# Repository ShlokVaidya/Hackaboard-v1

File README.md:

# 🎹 Hackaboard - The Hackaboard Keyboard

Welcome to **Hackaboard**, a beautifully crafted **63% mechanical keyboard** that combines aesthetics, functionality, and a touch of personality. A versatile keyboard designed to elevate your typing experience.

---

## ✨ What is Hackaboard?

Hackaboard is a custom mechanical keyboard featuring a 63% layout with modern conveniences like an **OLED display**, **rotary encoder**, and **full programmability**. Whether you're a developer, writer, designer, or gamer, this keyboard adapts to your workflow with support for multiple keymap configurations.

---

## 📸 Gallery

Take a look at the Hackaboard in all its glory:

---

## 🎯 Key Features

### Hardware Specs
- **Layout:** 63% compact form factor (63 keys)
- **Microcontroller:** Raspberry Pi Pico 2W (RP2350, supports QMK firmware)
- **Matrix:** 5 rows × 15 columns (COL2ROW configuration)
- **Switch Type:** Cherry MX PCB hotswap compatible
- **Display:** SSD1306 0.91" OLED (128x32 pixels)
- **Input:** EC11 Rotary Encoder with knob support
- **Debounce:** 5ms for reliable key registration

### Software Capabilities
- **Firmware:** QMK-compatible with custom configuration
- **Encoder:** Customizable rotary encoder with 4-level resolution
- **MIDI Support:** Full MIDI protocol implementation for music applications
- **Macros:** Built-in email address macro with right shift + 2
- **Keymaps:** Multiple pre-configured layouts (see below)

Please read [the Journal](./hackaboard-journal.md)
---

## ⌨️ Keymap Configurations

Hackaboard comes with **4 pre-built keymaps** to suit different typing styles and use cases:

### 1. **Default Keymap**
The standard ANSI layout – perfect for everyday typing and programming.

### 2. **Photographer Keymap**
Optimized for photo editing workflows with custom shortcuts and macro assignments.

### 3. **Writer Keymap**
Specialized layout for content creators with quick-access keys for common writing functions.

### 4. **VIA-Compatible Keymap**
Full support for the VIA configurator, allowing you to reprogram your keyboard without touching code.

---

# BOM table

Category | Item | Website | Cost (INR) | Cost (USD)
-- | -- | -- | -- | --
MCU | Raspberry Pi Pico 2 | Robu.in | ₹544 | $6
Diodes | 1N4148 SOD-123 (×63) | Robu.in | ₹36 | $0.4
Shipping (MCU + diodes) | — | Robu.in | ₹49 | $0.54
Subtotal (MCU + diodes) |   |   | ₹630 | $7
Conversion fee (3%) |   |   | ₹650 | $7.22
MCU + Diodes Total |   |   | ₹650 | $7.22
PCB | 2-layer PCB (base settings, incl. GST + shipping) | LionCircuits | ₹5,281 | $58.68
Conversion fee (3%) |   |   | ₹159 | $1.77
PCB Total |   |   | ₹5,440 | $60.45
Switches + Stabilizers + Hotswap sockets | (x45 + x10 pack) | StacksKB | ₹3,604 | $40.04
Conversion fee (3%) |   |   | ₹108 | $1.20
Switches Total |   |   | ₹3,712 | $41.24
Keycaps | Full keycap set | CuriosityCaps | ₹1,999 | $22.21
Conversion fee (3%) |   |   | ₹59 | $0.66
Keycaps Total |   |   | ₹2,058 | $22.87
Non-metal Plate | Plate | robu.in | Rs 330 | 3.6 USD
Screws | | onlyscrews.in | Rs 400 | 4.5 USD
0.91" OLED | | I have
Potentiometer | | I have

And i need 3d printing from #printing-legion so that's Rs 820 or **9 USD**.

## Total
Currency | Total
-- | --
INR | ₹13,400
USD | $147.25 

---

## 🛠️ File Structure

```
Hackaboard-v1/
├── keyboards/hackaboard/         # Main keyboard configuration
│   ├── config.h                  # Hardware configuration
│   ├── info.json                 # Layout and metadata
│   ├── hackaboard.c              # Firmware logic
│   ├── hackaboard.h              # Firmware headers
│   ├── rules.mk                  # Build rules
│   └── keymaps/                  # Keymap definitions
│       ├── default/              # Default layout
│       ├── photographer/         # Photo editing optimized
│       ├── writer/               # Content creation optimized
│       └── via/                  # VIA configurator support
├── PCB/                          # KiCAD PCB design files
│   ├── hackaboard.kicad_sch      # Schematic
│   ├── hackaboard.kicad_pcb      # PCB layout
│   └── production/               # Manufacturing files (BOM, positions)
├── CAD/                          # 3D models and mechanical design
│   ├── case/                     # Keyboard case designs
│   └── plate/                    # Stabilizer plate designs
└── images/                       # Product photography
```

---

## 🚀 Getting Started

### Prerequisites
- QMK Firmware environment set up ([QMK Docs](https://docs.qmk.fm/))
- Python 3.6+ and pip
- ARM GCC toolchain (for RP2350)

### Building the Firmware

1. **Clone the QMK repository** and copy the Hackaboard firmware:
   ```bash
   git clone https://github.com/qmk/qmk_firmware.git
   cp -r keyboards/hackaboard/ qmk_firmware/keyboards/
   ```

2. **Build your preferred keymap:**
   ```bash
   qmk compile -kb hackaboard -km default
   ```

3. **Flash to your keyboard:**
   ```bash
   qmk flash -kb hackaboard -km default
   ```

### VIA Support
If you prefer a graphical interface, use the **VIA configurator**:
1. Download [VIA](https://www.caniusevia.com/)
2. Load the VIA keymap onto your Hackaboard
3. Customize in real-time without reflashing

---

## 🎨 Customization

### Rotary Encoder
The EC11 encoder on Hackaboard can be customized for:
- Volume control
- Scroll wheel simulation
- Layer switching
- Application shortcuts

### OLED Display
The tiny 0.91" OLED shows:
- Current layer information
- Keyboard status
- Custom animations
- Typing statistics

### Email Macro
Quickly insert your email address:
- **Key Combo:** Right Shift + 2
- **Default:** `shlokvaidya.in@gmail.com.com` (customize in `config.h`)

---

## 🔧 Advanced Features

### MIDI Mode
Hackaboard supports MIDI communication for:
- Virtual instrument control
- DAW integration
- Music production workflows

### Debounce Tuning
Adjust key sensitivity without reflashing:
- Current debounce: 5ms
- Modify `DEBOUNCE` in `config.h` if needed

### Custom Firmware Logic
Edit `hackaboard.c` and `hackaboard.h` to add:
- Complex macros
- Display animations
- Sensor integrations
- Hardware customizations

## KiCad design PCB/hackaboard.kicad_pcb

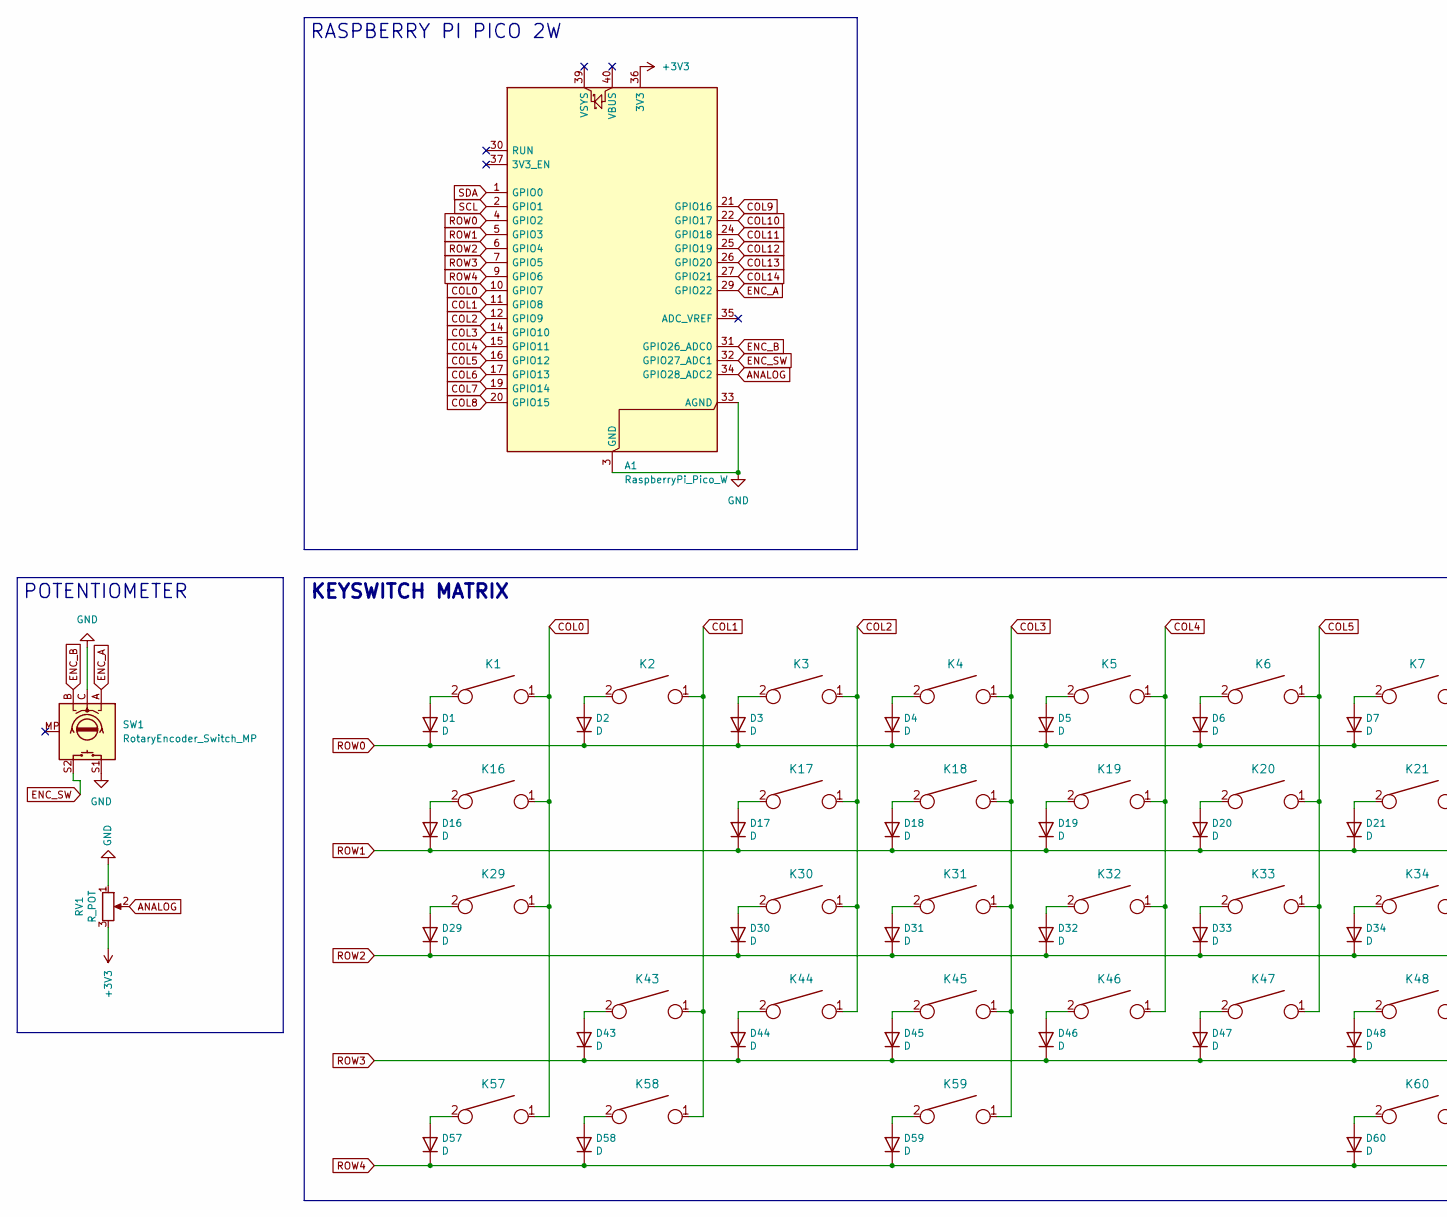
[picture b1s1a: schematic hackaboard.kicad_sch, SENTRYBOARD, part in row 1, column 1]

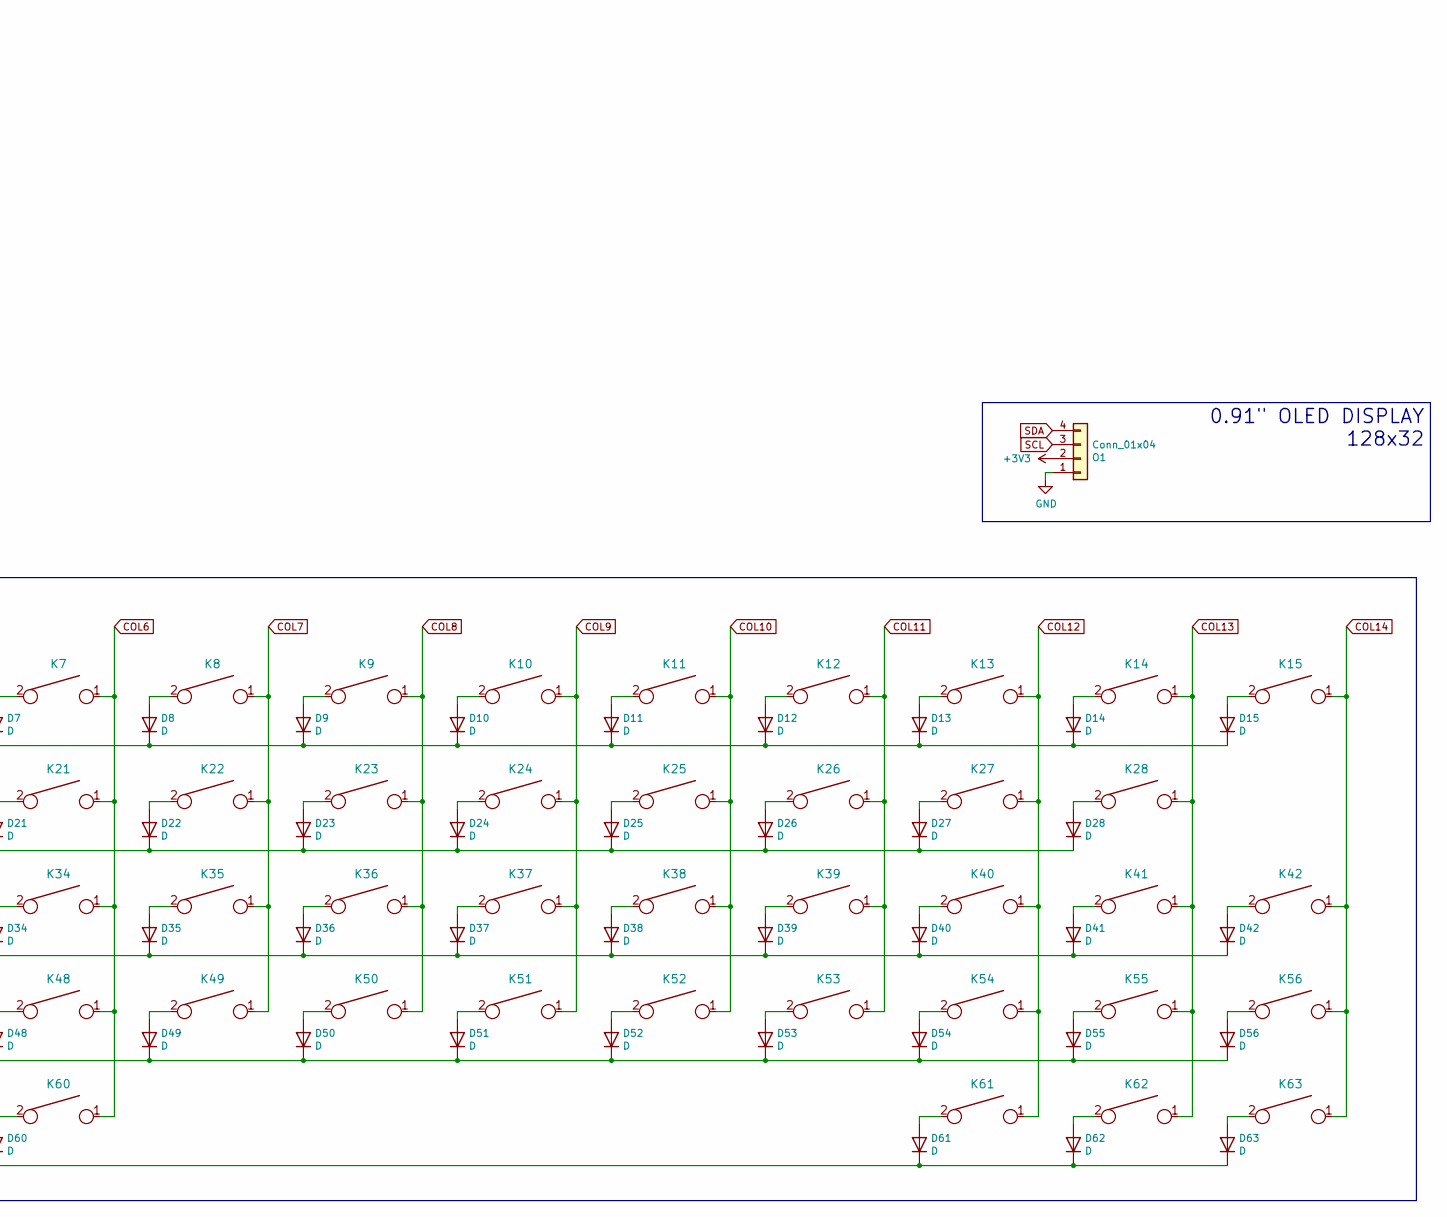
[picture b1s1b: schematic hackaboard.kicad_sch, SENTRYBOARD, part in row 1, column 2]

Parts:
A1: RaspberryPi_Pico_W; RaspberryPi_Pico_SMD_HandSolder
D1, D2, D3, D4, D5, D6, D7, D8, D9, D10, D11, D12, D13, D14, D15, D16, D17, D18, D19, D20, D21, D22, D23, D24, D25, D26, D27, D28, D29, D30, D31, D32, D33, D34, D35, D36, D37, D38, D39, D40, D41, D42, D43, D44, D45, D46, D47, D48, D49, D50, D51, D52, D53, D54, D55, D56, D57, D58, D59, D60, D61, D62, D63: D; D_SOD-123
K1, K2, K3, K4, K5, K6, K7, K8, K9, K10, K11, K12, K13, K14, K15, K17, K18, K19, K20, K21, K22, K23, K24, K25, K26, K27, K28, K30, K31, K32, K33, K34, K35, K36, K37, K38, K39, K40, K41, K44, K45, K46, K47, K48, K49, K50, K51, K52, K53, K54, K55, K56, K61, K62, K63: KEYSW; MXOnly-1U-Hotswap
K16: KEYSW; MXOnly-1.5U-Hotswap
K29: KEYSW; MXOnly-1.75U-Hotswap
K42: KEYSW; MXOnly-ISO-Hotswap
K43: KEYSW; MXOnly-2U-Hotswap-ReversedStabilizers
K57, K58, K59: KEYSW; MXOnly-1.25U-Hotswap
K60: KEYSW; MXOnly-6.25U-Hotswap-ReversedStabilizers
O1: Conn_01x04; SSD1306-0.91-OLED-4pin-128x32
RV1: R_POT; potentiometer_slider_45mm
SW1: RotaryEncoder_Switch_MP; RotaryEncoder_Alps_EC11E-Switch_Vertical_H20mm

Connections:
+3V3: A1.36 (3V3), O1.2, RV1.3
ANALOG: A1.34 (GPIO28_ADC2), RV1.2
COL0: A1.10 (GPIO7), K1.1, K16.1, K29.1, K57.1
COL1: A1.11 (GPIO8), K2.1, K43.1, K58.1
COL2: A1.12 (GPIO9), K3.1, K17.1, K30.1, K44.1
COL3: A1.14 (GPIO10), K4.1, K18.1, K31.1, K45.1, K59.1
COL4: A1.15 (GPIO11), K5.1, K19.1, K32.1, K46.1
COL5: A1.16 (GPIO12), K6.1, K20.1, K33.1, K47.1
COL6: A1.17 (GPIO13), K7.1, K21.1, K34.1, K48.1, K60.1
COL7: A1.19 (GPIO14), K8.1, K22.1, K35.1, K49.1
COL8: A1.20 (GPIO15), K9.1, K23.1, K36.1, K50.1
COL9: A1.21 (GPIO16), K10.1, K24.1, K37.1, K51.1
COL10: A1.22 (GPIO17), K11.1, K25.1, K38.1, K52.1
COL11: A1.24 (GPIO18), K12.1, K26.1, K39.1, K53.1
COL12: A1.25 (GPIO19), K13.1, K27.1, K40.1, K54.1, K61.1
COL13: A1.26 (GPIO20), K14.1, K28.1, K41.1, K55.1, K62.1
COL14: A1.27 (GPIO21), K15.1, K42.1, K56.1, K63.1
ENC_A: A1.29 (GPIO22), SW1.A
ENC_B: A1.31 (GPIO26_ADC0), SW1.B
ENC_SW: A1.32 (GPIO27_ADC1), SW1.S2
GND: A1.3 (GND), A1.8 (GND), A1.13 (GND), A1.18 (GND), A1.23 (GND), A1.28 (GND), A1.33 (AGND), A1.38 (GND), O1.1, RV1.1, SW1.C, SW1.S1
unnamed: D1.2 (A), K1.2
unnamed: D2.2 (A), K2.2
unnamed: D3.2 (A), K3.2
unnamed: D4.2 (A), K4.2
unnamed: D5.2 (A), K5.2
unnamed: D6.2 (A), K6.2
unnamed: D7.2 (A), K7.2
unnamed: D8.2 (A), K8.2
unnamed: D9.2 (A), K9.2
unnamed: D10.2 (A), K10.2
unnamed: D11.2 (A), K11.2
unnamed: D12.2 (A), K12.2
unnamed: D13.2 (A), K13.2
unnamed: D14.2 (A), K14.2
unnamed: D15.2 (A), K15.2
unnamed: D16.2 (A), K16.2
unnamed: D17.2 (A), K17.2
unnamed: D18.2 (A), K18.2
unnamed: D19.2 (A), K19.2
unnamed: D20.2 (A), K20.2
unnamed: D21.2 (A), K21.2
unnamed: D22.2 (A), K22.2
unnamed: D23.2 (A), K23.2
unnamed: D24.2 (A), K24.2
unnamed: D25.2 (A), K25.2
unnamed: D26.2 (A), K26.2
unnamed: D27.2 (A), K27.2
unnamed: D28.2 (A), K28.2
unnamed: D29.2 (A), K29.2
unnamed: D30.2 (A), K30.2
unnamed: D31.2 (A), K31.2
unnamed: D32.2 (A), K32.2
unnamed: D33.2 (A), K33.2
unnamed: D34.2 (A), K34.2
unnamed: D35.2 (A), K35.2
unnamed: D36.2 (A), K36.2
unnamed: D37.2 (A), K37.2
unnamed: D38.2 (A), K38.2
unnamed: D39.2 (A), K39.2
unnamed: D40.2 (A), K40.2
unnamed: D41.2 (A), K41.2
unnamed: D42.2 (A), K42.2
unnamed: D43.2 (A), K43.2
unnamed: D44.2 (A), K44.2
unnamed: D45.2 (A), K45.2
unnamed: D46.2 (A), K46.2
unnamed: D47.2 (A), K47.2
unnamed: D48.2 (A), K48.2
unnamed: D49.2 (A), K49.2
unnamed: D50.2 (A), K50.2
unnamed: D51.2 (A), K51.2
unnamed: D52.2 (A), K52.2
unnamed: D53.2 (A), K53.2
unnamed: D54.2 (A), K54.2
unnamed: D55.2 (A), K55.2
unnamed: D56.2 (A), K56.2
unnamed: D57.2 (A), K57.2
unnamed: D58.2 (A), K58.2
unnamed: D59.2 (A), K59.2
unnamed: D60.2 (A), K60.2
unnamed: D61.2 (A), K61.2
unnamed: D62.2 (A), K62.2
unnamed: D63.2 (A), K63.2
ROW0: A1.4 (GPIO2), D1.1 (K), D2.1 (K), D3.1 (K), D4.1 (K), D5.1 (K), D6.1 (K), D7.1 (K), D8.1 (K), D9.1 (K), D10.1 (K), D11.1 (K), D12.1 (K), D13.1 (K), D14.1 (K), D15.1 (K)
ROW1: A1.5 (GPIO3), D16.1 (K), D17.1 (K), D18.1 (K), D19.1 (K), D20.1 (K), D21.1 (K), D22.1 (K), D23.1 (K), D24.1 (K), D25.1 (K), D26.1 (K), D27.1 (K), D28.1 (K)
ROW2: A1.6 (GPIO4), D29.1 (K), D30.1 (K), D31.1 (K), D32.1 (K), D33.1 (K), D34.1 (K), D35.1 (K), D36.1 (K), D37.1 (K), D38.1 (K), D39.1 (K), D40.1 (K), D41.1 (K), D42.1 (K)
ROW3: A1.7 (GPIO5), D43.1 (K), D44.1 (K), D45.1 (K), D46.1 (K), D47.1 (K), D48.1 (K), D49.1 (K), D50.1 (K), D51.1 (K), D52.1 (K), D53.1 (K), D54.1 (K), D55.1 (K), D56.1 (K)
ROW4: A1.9 (GPIO6), D57.1 (K), D58.1 (K), D59.1 (K), D60.1 (K), D61.1 (K), D62.1 (K), D63.1 (K)
SCL: A1.2 (GPIO1), O1.3
SDA: A1.1 (GPIO0), O1.4

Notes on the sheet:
POTENTIOMETER
RASPBERRY PI PICO 2W
0.91" OLED DISPLAY 128x32
KEYSWITCH MATRIX

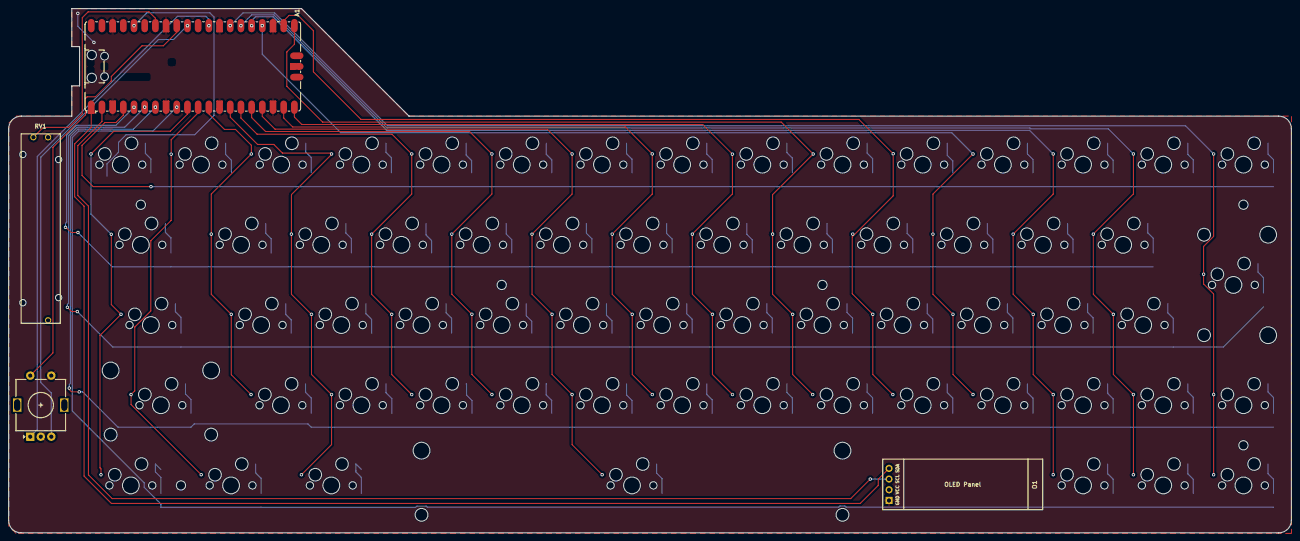
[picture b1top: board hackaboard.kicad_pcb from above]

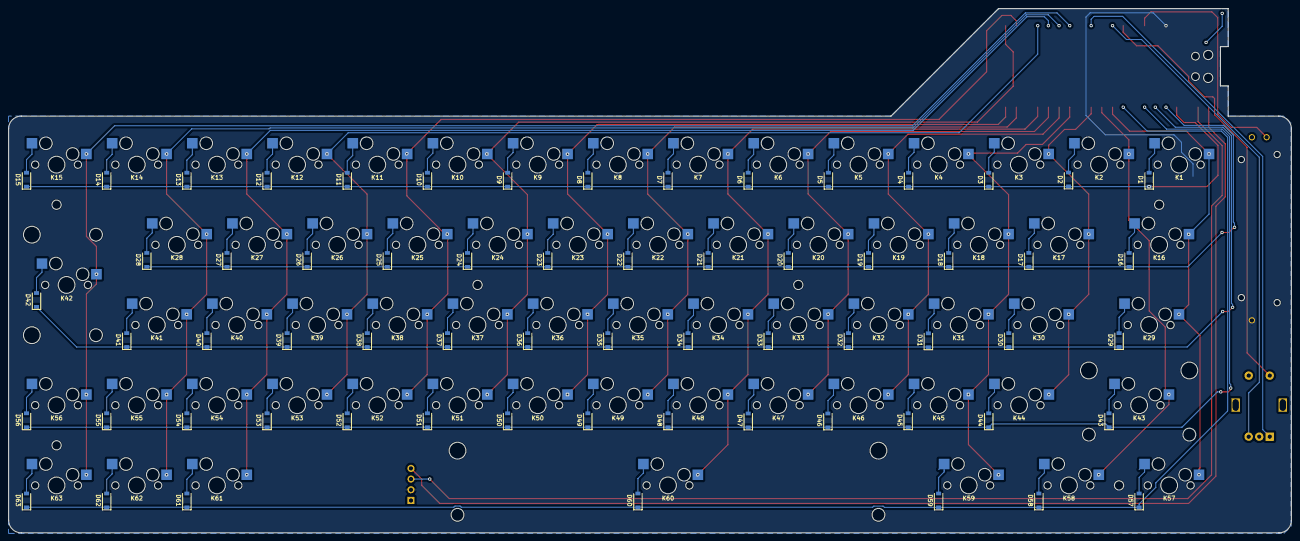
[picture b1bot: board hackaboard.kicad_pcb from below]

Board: 2 copper layers, 304.7 x 124.5 mm, 136 parts (63 on the bottom side), 91 nets.

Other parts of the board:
[SCREW]: MountingHole_2.2mm_M2
[SCREW]#2, [SCREW]#3, [SCREW]#4, [SCREW]#5, [SCREW]#6: MountingHole_2.2mm_M2

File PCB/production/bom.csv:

Designator,Footprint,Quantity,Value,LCSC Part #
A1,RaspberryPi_Pico_SMD_HandSolder,1,RaspberryPi_Pico_W,
"D1, D10, D11, D12, D13, D14, D15, D16, D17, D18, D19, D2, D20, D21, D22, D23, D24, D25, D26, D27, D28, D29, D3, D30, D31, D32, D33, D34, D35, D36, D37, D38, D39, D4, D40, D41, D42, D43, D44, D45, D46, D47, D48, D49, D5, D50, D51, D52, D53, D54, D55, D56, D57, D58, D59, D6, D60, D61, D62, D63, D7, D8, D9",D_SOD-123,63,D,
"K1, K10, K11, K12, K13, K14, K15, K17, K18, K19, K2, K20, K21, K22, K23, K24, K25, K26, K27, K28, K3, K30, K31, K32, K33, K34, K35, K36, K37, K38, K39, K4, K40, K41, K44, K45, K46, K47, K48, K49, K5, K50, K51, K52, K53, K54, K55, K56, K6, K61, K62, K63, K7, K8, K9",MXOnly-1U-Hotswap,55,KEYSW,
K16,MXOnly-1.5U-Hotswap,1,KEYSW,
K29,MXOnly-1.75U-Hotswap,1,KEYSW,
K42,MXOnly-ISO-Hotswap,1,KEYSW,
K43,MXOnly-2U-Hotswap-ReversedStabilizers,1,KEYSW,
"K57, K58, K59",MXOnly-1.25U-Hotswap,3,KEYSW,
K60,MXOnly-6.25U-Hotswap-ReversedStabilizers,1,KEYSW,
O1,SSD1306-0.91-OLED-4pin-128x32,1,Conn_01x04,
RV1,potentiometer_slider_45mm,1,R_POT,
SW1,RotaryEncoder_Alps_EC11E-Switch_Vertical_H20mm,1,RotaryEncoder_Switch_MP,

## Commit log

2026-01-13 Hackaboard
2026-01-13 Debuggung
2026-01-14 Added Journal
2026-01-14 ReadMe
